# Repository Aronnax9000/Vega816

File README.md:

# Vega816 - Dual 65C816 Computer with Vector Pull rewrite

## Table of Contents

* [Functional Description](#functional-description)
* [CPU Buffer Board](#cpu-buffer-board)
* [DMA Control and Vector Pull Rewrite Shim](#dma-control-and-vector-pull-rewrite-shim)
    * [DMA Control Shim](#dma-control-shim)
    * [Vector Pull Rewrite Shim](#vector-pull-rewrite-shim)
    * [Offset of 7 triggers RESB interrupt handler for W65C816](#offset-of-7-triggers-resb-interrupt-handler-for-w65c816)
    * [Details of Vector Pull address rewriting](#details-of-vector-pull-address-rewriting)
    * [Effect of Vector Pull Rewrite in Emulation (65C02) Mode](#effect-of-vector-pull-rewrite-in-emulation-65c02-mode)
* [IRQ Dispatcher](#irq-dispatcher)
    * [IRQ Priority 7 to NMI Option](#irq-priority-7-to-nmi-option)
* [DMA Controller](#dma-controller)
    * [DMA Channels and Address Interleaving](#dma-channels-and-address-interleaving)
    * [How the DMA Controller routes requests](#how-the-dma-controller-routes-requests)
    * [DMA Request timing](#dma-request-timing)
* [Quad 64B I/O Bus](#quad-64b-i-o-bus)
* [Programmable Interrupt Controller (PIC)](#programmable-interrupt-controller-pic)
    * [2 Device PIC](#2-device-pic)
    * [Quad 2-Device PIC](#quad-2-device-pic)
* [16 MB Memory Decoder and Bus](#16-mb-memory-decoder-and-bus)
* [4 MB RAM + 32 K EEPROM Module](#4-mb-ram-32-k-eeprom-module)
* [Expansion Port to Single Device Ports](#expansion-port-to-single-device)
* [Single Device Port Breakouts](#single-device-port-breakouts)
* [Devices](#devices)
    * [W65C22 VIA Port](#w65c22-via-port)
    * [W65C51N ACIA (RS-232)](#w65c51n-acia-rs-232)
    * [8580/6581 SID](#8580-6581-sid)

* [VIA Port Devices](#via-port-devices)
    * [2x16 Character Display and front panel switches](#2x16-character-display-and-front-panel-switches)
    * [System Controller / SPI Controller](#system-controller-spi-controller)
    * [Ben Eater PS/2 Interface](#ben-eater-ps-2-interface)
    * [Commodore 64 CIA (VIA) #1](#commodore-64-cia-via-1)

## Functional Description

The Vega816 is a modular architecture for implementing symmetrical multiprocessing (SMP) with the Western Design Center W65C816 Microprocessor (aka 65816). The project takes as its starting point the 65816 breakout board designed by Adrien Kohlbecker, documented at [the project's GitHub page](https://github.com/adrienkohlbecker/BB816) as well as [Adrien's YouTube series](https://www.youtube.com/playlist?list=PLdGm_pyUmoII9D16mzw-XsJjHKi3f1kqT).

Support is provided for up to four bus mastering devices (four CPUs, or three CPUs and a video card) accessing up to four DMA channels, mapped into each CPU's address space.

## CPU Buffer Board

The CPU Buffer board provides two straight-wired connectors for the BB816 CPU breakout board, called "the CPU end", and buffers communications between the two of them and dual output connectors with the same pinout, called "the DMA end".

The extra straight wired connectors are included for ease of stacking the boards, both on the CPU end, and on the DMA end, in a multiplexed configuration, to implement shared memory multiprocessing. 

The circuit uses a 74AHCT245 octal bus transceiver for bi-directional communication for the 8 data lines, and seven 74HC541 octal buffers for the remaining signals provided by the BB816 CPU breakout board, including VPA and VDA. One of the buffers is allocated to CPU inputs (NMIB, IRQB, ABORTB, RDY_IN, etc), buffering signals from the DMA end. The remaining 74HC541s buffer lines from the CPU end onto the DMA end.

The bus transceiver and buffers' output enable lines are tied together and provided as an active low input called DMAB, so that a single signal suffices to turn communication on and off. A 1K pulldown resistor ensures that the board is active unless DMAB is raised high by external hardware.

## DMA Control and Vector Pull Rewrite Shim

If we assign each DMA channel its own address space, we can use address decoding in order to select which DMA channel is to be accessed by a particular CPU. In order to do that, we need to intercept the address lines from the CPU, pass decoding information to the DMA controller, and potentially rewrite the address being asserted by the CPU, before granting the CPU buffer access to the correct DMA channel.

The W65C816's VPB (Vector Pull) line also allows rewriting of the address asserted by the CPU when it is pulling an interrupt vector. It is convenient to provide hardware to intercept and rewrite the vector pull address as part of the same adapter.

Together, the DMA Control Shim and the Vector Pull Rewrite Shim provide facilities for DMA control and Vector Pull Rewrite to be performed by external hardware. 

### DMA Control Shim

The DMA Control shim provides movable jumpers for each of the bits A16-A23. Any of the bits may be selected as DMA_REQ. Once the jumper has been set to select one of those lines, it is connected as the DMA_REQ output, and disconnected from output to the DMA end, and is in fact pulled low on the DMA end (10K resistor), in order to map the request into a lower part of the DMA channel's address space.

The jumper offers the user a choice of granularity of DMA channel address mapping, in multiple of 2 increments from 64K (single bank, the minimum granularity) to 4M maximum. This allows for the address space to be contiguous across all DMA channels, depending on installed memory sizes. Ordinarily, this jumper should be set to the size of the maximum address space serviced by the hardware on either DMA channel, e.g. the total installed memory on that channel, or half the total memory across the two channels.

### Vector Pull Rewrite Shim

The Vector Pull Rewrite shim allows the IRQ Dispatcher to alter the fetch address of the processor when it is fetching an IRQ vector. A three bit number between 0-7 is added to the least significant bits (but one) of the fetch address, A1-A3, with carry into A4.

The VPB line is brought active low by the 65C816 during the fetch of any interrupt vector, not just IRQ. However, the standard IRQ vector's address has a unique bit pattern which makes it easy to autodetect, so that the shim will only request a vector pull offset when fetching the IRQ vector, and not for any other kind of interrupt.

When VPB is active (low) and A1-A3 are all high, indicating that an interrupt vector is being fetched by the processor, the shim requests a vector pull offset from the IRQ Dispatcher by asserting VP_REQ (positive logic). Pulldown resistors keep the offset equal to zero when Y0-Y2 are not connected (no IRQ Dispatcher) or in a high impedance state. 

A 74HC283 adder is used to add an offset to A1-A4 equal to the three bit number provided as input to the shim from the IRQ Dispatcher, on pins Y0-Y2. This has the effect of altering the fetch of the IRQ vector at $FFEE to a fetch of a vector at one of the following eight addresses: 
```
$00FFEE IRQ 0 
$00FFF0 IRQ 1 
$00FFF2 IRQ 2 
$00FFF4 IRQ 3 
$00FFF6 IRQ 4 
$00FFF8 IRQ 5 
$00FFFA IRQ 6 
$00FFFC RESET 
```
Y0-Y2 are pulled low by 10K resistors, for cases in which no Vector Pull controller is connected. Bypass jumpers are also provided for A1-A4, in case the 74HC283 adder and supporting logic are not installed.

The connector for the external Vector Pull Rewrite controller provides the E signal from the CPU, so that the Vector Pull Rewrite controller can know which scheme of vector pull (W65C02, W65C816) is being used.

#### Exposure of NMI and IRQ

The Vector Pull Rewrite shim exposes both IRQ and NMI to the IRQ Dispatcher. 

If the IRQ Dispatcher is not installed, a jumper on the Quad 64 IO Bus (IRQ Dispatch Bypass) should be installed to route IRQs to the common IRQ signal on the CPU via the CPU Buffer's DMA Channel connector.

When the IRQ Dispatcher is installed, the dispatcher takes responsibility for issuing IRQ to the CPU, via the Vector Pull Rewrite shim.

The exposure of NMI allows a device to raise an  IRQs at a selected IRQ priority level (say, IRQ 7) and instead trigger NMI, as the Commodore 64 RESTORE key did. The assertion of NMI is left under the control of the IRQ Dispatcher.

In scenarios where the IRQ Dispatcher is not installed, a jumper on the Quad 64B IO Bus (NMI Dispatch Bypass) can be used to direct IRQA7, IRQB7, both, or neither, to NMI.

#### Offset of 7 triggers RESB interrupt handler for W65C816

Note that, when the 65816 is running in native mode, if an IRQ priority of 7 (0x111) is asserted on Y0-Y2, the vector offset will result in the RESET vector being pulled. Since no actual hardware reset has occurred, if the reset handler relies on a hardware reset having taken place, unpredictable state may occur. It is generally advised to avoid the use of IRQ priority 7 when the CPU is in native mode. Alternatively, IRQ priority 7 may be rerouted to NMI, either through the IRQ Dispatcher, or a jumper on the Quad 64B IO Bus.

#### Details of Vector Pull address rewriting
The W65C816 datasheet gives this table of interrupt vectors which lie between $00FFE4 and $00FFFC
```
Address Function Last Octet (binary)
$00FFE4 COP      0x1110 0100
$00FFE6 BRK      0x1110 0110
$00FFE8 ABORT    0x1110 1000
$00FFEA NMI      0x1110 1010
$00FFEE IRQ      0x1110 1110
$00FFFC RESET    0x1111 1100
```
The datasheet also specifies that when the 65C816 is addressing an interrupt vector, it pulls its VPB line low. This is to allow the system to override the fetched interrupt vector with any other. 

VPB is pulled low for any interrupt vector fetch, not just IRQ, but the present design purposefully limits Vector Pull rewriting to only those cases when IRQ is the vector being fetched.

Note that the last nybble of each of the standard interrupt vectors is unique, which aids in designing a hook for any one of them (the same is true for 6502 Emulation mode, see below). A test of these four bits suffices to uniquely identify the vector being pulled. In particular, both bytes of the two-byte IRQ vector ($FFEE and $FFEF) are the only two bytes in this table with $E or $F (0x1110, 0x1111) as the last nybble of address, i.e., A1-A3 high.

Note also the gap of 12 bytes between the IRQ vector and the RESET vector. Since each vector occupies two bytes, this gap provides sufficient space to specify six (6) additional vectors. 

```
$00FFE4 COP	
$00FFE6 BRK
$00FFE8 ABORT 
$00FFEA NMI 
$00FFEE IRQ 0 
$00FFF0 IRQ 1 
$00FFF2 IRQ 2 
$00FFF4 IRQ 3 
$00FFF6 IRQ 4 
$00FFF8 IRQ 5 
$00FFFA IRQ 6 
$00FFFC RESET 
```
If an offset 0-6 is added to A1-A3, (leaving A0 as found), then the vector fetched will be as shown above, going forward from IRQ0.

#### Effect of Vector Pull Rewrite in Emulation (65C02) Mode
The 6502's IRQ vector, like its 65816 counterpart, has 0x111x in the last nybble, so it is detected by the Vector Pull Rewrite Shim. 
```
$FFFA NMI
$FFFC RESB
$FFFE BRK/IRQ 
```
Unlike the 65816's IRQ vector, the 6502 IRQ vector occurs at the very top of its page, so additions of 1-7 to the bits may force A4 to overflow to 0 (no carry). In particular, $FFFE + $02 = $FFE0, etc. This means the augmented
IRQ vector map for the 6502 looks like this:

```
$FFE0 BRK/IRQ 1
$FFE2 BRK/IRQ 2
$FFE4 BRK/IRQ 3
$FFE6 BRK/IRQ 4
$FFE8 BRK/IRQ 5
$FFEA BRK/IRQ 6
$FFEC BRK/IRQ 7
...
$FFFA NMI
$FFFC RESB
$FFFE BRK/IRQ 0
```
## IRQ Dispatcher

Devices mapped within the physical address space of either DMA channel may raise interrupt requests against either CPU. For each CPU, an 8-to-3 priority encoders is used to prioritize eight different levels of IRQ, from 0-7, with lower values meaning higher priority.

The priority is encoded as a three bit offset and offered to the Vector Pull Rewrite shim, on pins Y0-Y2, where it is used to offset the fetch addresses of the CPU's next two-byte IRQ vector pull. 

IRQs received from DMA channel 0 and intended for CPU A or CPU B will be routed to those CPUs. 

For IRQs received from DMA channel 1, the situation is reversed: IRQs which DMA channel 1 intended for CPU A will be routed to CPU B, and vice versa. This crossover in routing means that the CPU target values in the system's PIC controllers always refer to the same physical CPU. I.e., CPU A is always target 0, and CPU B is always target 1, no matter on which DMA channel a PIC is installed. The crossover is reflected in the connector placement on the IRQ Dispatcher: no crossover cable is needed.

### IRQ Priority 7 to NMI Option

The combined IRQ signals are diode-NANDed together to drive IRQ on the CPU through the Vector Pull Rewrite shim. IRQ priorities 0-6 are NANDed together first, with priority 7 NANDed to the result unless jumper IRQA7 or IRQB7 are set to direct priority 7 to NMI to CPU A or CPU B.

Rerouting IRQ Priority 7 to NMI is offered elsewhere in the design, as a jumper on the Quad 64B IO Bus, for cases where no IRQ Dispatcher and/or Vector Pull Rewrite shim is installed. See the documentation on the Quad 64B IO Bus.

## DMA Controller

The DMA Controller is intended to control the multiplexing of one or two CPUs (called CPU A and CPU B) onto one or two communication channels (called DMA 0 and DMA 1). The two channels are cross-mapped in address space from the point of view of opposite processors, depending on a selected granularity. For example, if 64 KB (single bank) granularity is selected, when CPU A requests Bank 0, the DMA controller will connect it to DMA channel 0, whereas if CPU A requests Bank 1, the controller will connect it to DMA channel 1. The situation is reversed for CPU B. The controller will direct its requests for Bank 0 to DMA channel 1, and requests for Bank 1 to DMA channel 0.

This permits each CPU to have its Bank 0 lie within the address space of a separate physical DMA channel, so that accesses by each CPU to its own Bank 0 will not normally interfere with the opposite CPU's requests for its own Bank 0.

The effect for higher memory is that each CPU's odd numbered banks are the other CPU's even numbered banks, interleaved to the top of physical memory.

The granularity of the interleaving is specified by a jumper on the DMA Controller Shim, and provided to the DMA controller as the signal DMA_REQ. Additionally, the following CPU signals are utilized in implementing DMA:
```
RDY_IN
ABORTB
VA
```
Since the DMA controller will dispatch requests from up to two CPUs, CPU A and CPU B, the signals are distinguished within the controller with these designations:

Inputs
```
DMA_REQB_A DMA_REQB_A
RDY_IN_A  RDY_IN_B
ABORTB_A  ABORTB_B
VA_A      VA_B
```
Since the DMA channels are cross-mapped in address range between the two CPUs, so that each CPU's DMA 0 corresponds to the lower part of its address space with respect to DMA 1, the outputs are:
```
DMA_0_A  = DMA_1_B
DMA_1_A  = DMA_0_B
```
This cross mapping, which takes place in the connector wiring of the DMA Controller board, means that two identically configured units may be connected as CPU A or CPU B, provided that their DMA buffer modules are connected with the sense of DMA 0 and DMA 1 reversed.

The "home" channel for a CPU is the DMA channel containing that CPU's Bank Zero.

Here are the possible scenarios for DMA arbitration:

1. Both CPUs are asserting valid address, each against their own home DMA channels. CPU A is using DMA 0, and CPU B is using DMA 1.
2. Both CPUs are asserting valid address, against the opposite CPU's home DMA channel. CPU A is asserting against DMA 1, and CPU B is asserting against DMA 0.
3. Both CPUs are asserting valid address against the same DMA channel. CPU A is asserting against DMA 0, and so is CPU B.
4. Both CPUs are asserting valid address against the same DMA channel. CPU A is asserting against DMA 1, and so is CPU B.

The DMA controller monitors the VA (Valid Address) from one or two CPUs, as well as an additional input, DMA_REQB. If one CPU asserts DMA_REQB, the controller checks the VA line from the opposite CPU. If it is not active, the controller asserts DMA

### DMA Channels and Address Interleaving

When no request granularity is set for a CPU on the DMA Control Shim, all DMA requests take place against DMA 0.

If only the primary granularity is set, DMA requests will take place against DMA 0 and DMA 2.
If only the secondary granularity is set, DMA requests will take place against DMA 0 and DMA 1.

If both granularities are set, DMA requests will take place against DMA 0-3. The maximum granularity for four channel DMA is 4 MB, with primary set at 8 MB and secondary set at 4MB. (0x1100 0000). In that case,

```
Requests for the range 
(0x00?? ????) go to DMA channel 0
(0x01?? ????) go to DMA channel 1
(0x10?? ????) go to DMA channel 2
(0x11?? ????) go to DMA channel 3
```

The DMA controller maps requests so that each CPU sees a different DMA channel as its channel 0, with subsequent channels in order. The next CPU's channel 0 is the present CPU's channel 1, and channel 0 for the next CPU after that is channel 2. The order wraps to form a closed ring.

```
           Requested           Physical
CPU   A    B      C      D
      0    1      2      3      DMA 0
      1    2      3      0      DMA 1
      2    3      0      1      DMA 2
      3    0      1      2      DMA 3
```

From the chart it can be seen that the channel that CPU A sees as DMA 0 is seen by CPU B as DMA channel 3, etc.

DMA request granularity may or may not match the largest installed address size.

Since the address bits used to select the DMA channels are suppressed in the address presented to the destination channel, if a CPU's request granularity is set to a smaller value than the installed memory size on any given DMA channel, then a range of that memory will not be accessible to that CPU.

CPU A has primary DMA on 1M, and secondary DMA set to 512K. 
CPU A issues requests against Banks 0 to 7.

What DMA channels are addressed?

```
0x000 Bank 0x000 0 on DMA 0
0x001 Bank 0x000 0 on DMA 1
0x010 Bank 0x000 0 on DMA 2
0x011 Bank 0x000 0 on DMA 3
0x100 Bank 0x100 4 on DMA 0
0x101 Bank 0x100 4 on DMA 1
0x110 Bank 0x100 4 on DMA 2
0x111 Bank 0x100 4 on DMA 3
```

### How the DMA Controller routes requests

Each request enters the DMA controller as a two bit code, representing the two address lines selected by jumper settings on the DMA Control Shim. These two bits are augmented with a third bit, a CPU Priority bit supplied for that CPU. The CPU Priority bit is active low, and pulled high. 

The three bit request is decoded into a one in eight choice, each representing a request for one of four DMA channels, with and without priority. The eight decoded request lines are then routed, together with the decoded request lines from the other CPUs, into priority encoders, one for each of the four DMA channels. The eight request lines entering each DMA channel's priority encoder are wired so that the four priority requests occur with highest priority, followed by the four no-priority request lines. Among the two sets of priority requests, Each DMA channel gives greatest priority to a particular CPU, followed by the others in ring order.

```
DMA Channel   Order
     0        ADCB                  
     1        BADC            
     2        CBAD
     3        DCBA            
```

When more than one CPU requests the same DMA channel, the losing CPU(s) must be informed, since they will not have access to the DMA channel for the duration of the current clock cycle. 

The W65C816 provides two mechanisms for this, the READY signal, and the ABORTB interrupt signal. The READY signal pauses the processor, if pulled low. Releasing the low condition, allowing READY to return high, will cause the CPU to resume processing on the rising edge of the next clock cycle.

Adrien Kohlbecker's BB816 CPU breakout provides the input to the READY signal as RDY_IN. This signal is that which is used by the DMA Controller to pause the CPU.

If the losing CPU is losing access to its Bank Zero channel (due to the winning CPU having priority bit active), the losing CPU is paused, by pulling RDY_IN low. 

Any other losing CPU is informed by pulling the losing CPU's ABORTB low, triggering the losing CPU's ABORT Interrupt handler. In most cases, the handler will simply return control to the interrupted process so that another attempt at access to the DMA channel can be made on the next clock cycle.

### DMA Request timing

CPU to DMA routing must be complete, with time to spare for the devices on the DMA channel to decode incoming address, before the routing is latched in on the falling edge of the clock. Now latched, the CPU to DMA channel routing persists through the remainder of the clock cycle, until unlatched at the rising edge of the clock at the beginning of the next cycle, so that arbitration may begin again.

## Quad 64B I/O Bus
The I/O bus board decodes a selected page (256 bytes) of address space for device I/O, together with a corresponding range in the the page immediately above it, for use by I/O devices.
3
Jumpers set the base I/O address space on any even-numbered page boundary in Bank Zero. The page of address space immediately above the base I/O page is reserved for configuring the programmable interrupt controller (PIC). For example, if the bus is set so that its base address is $0200, then page $0300 is reserved for use by the PIC.

The odd numbered page immediately above the base page is used by the programmable interrupt controller to store IRQ priority and CPU target information for use in forwarding interrupt requests issued by devices under PIC control.

In order to avoid the default page zero and stack areas at $0000 and $01000, it is advisable to avoid setting the I/O base address to page $00, leaving 63 possible pages between $0200-$7E00.

Four I/O expansion ports are provided, each spanning 64 bytes of the assigned I/O page. Each port is provided with a one-in-four chip select signal based on further decoding of the address, into 16 byte ranges areas. 
Standard connections are provided for adding a CS Decode module which can perform finer and/or coarser grained address decoding into 64, 32, and 8 byte I/O address ranges.

The 16 byte range chip select signals are raised high for both the I/O page within that 16 byte range, as well as for that range in the page immediately above it. E.g., if a device is mapped to $0210-$021F, then the chip select for that device is also active for the range $0310-$031F. This allows access to latches used to store programmable interrupt configuration, and potentially other metadata used in controlling the device.

The 16 IRQ output lines from each expansion port (8 priorities destined for one of up to two CPUs) are multiplexed via diode logic for dispatch by the IRQ Dispatch board.

## Programmable Interrupt Controller (PIC)

### 2 Device PIC
The programmable interrupt controller accepts active low IRQ inputs from up to two sources. For each source, the PIC generates an interrupt signal at one of eight pre-selectable priorities (0-7), and directs the interrupt to a preselected one of two target CPUs. The PIC uses diode logic so that interrupts generated by multiple PICs may be placed on the same IRQ bus. 

The IRQ bus terminates at the IRQ Dispatcher, where 10K pull-up resistors ensure that lines on the IRQ bus are held high, unless pulled low by an interrupt signal originating at a PIC.

### Quad 2-Device PIC
A 64-byte expansion slot may include a programmable interrupt controller. The PIC subdivides the 64 byte address range into eight 8-byte device I/O spaces, two for each of the 16-byte address ranges decoded by the expansion bus controller and supplied to the PIC as chip select lines. 

Both IRQ priority (0-7) and CPU destination (CPU A or CPU B) can be programmed for each of up to eight devices, by writing to latches which shadow the device I/O space in the next higher page of address space. Four octal latches, at address offsets +$100, +$104, +$108 and +$10C offsets from the corresponding 16 byte I/O address ranges are provided. Each octal latch stores programmable interrupt information for up to two 8 byte devices: the low nybble for an eight byte device at offset +$00 from the base I/O address, and the high nybble for an eight byte device at offset $08 from the base I/O address. The low bit of the nybble determines the target CPU. The high three bits specify the priority from 0-7.

## 16 MB Memory Decoder and Bus

## 4 MB RAM + 32 K EEPROM Module

## Expansion Port to Single Device

The 64-byte expansion slots provided by the Expansion Bus may be broken out into individual device I/O ports spanning 64, 32, 16, or 8 bytes of address space. The four 16-byte chip select lines are further decoded by the programmable interrupt controller down to two 8-byte chip select lines per 16 byte range.

These sample breakouts show a complete breakout of one port into 1x64, 2x32, 4x16 and 8x8 byte device ports. Also shown is a reduction of this most general breakout into a sample breakout capable of supporting 3 VIAs and 2 ACIAs.

## Single Device Port Breakouts
A single 64, 32, or 16 byte device port may be further adapted to serve multiple devices of smaller address range. This approach introduces an extra address decoding delay compared with the above approach of adapting expansion bus directly.

## Devices

### W65C22 VIA Port

This device presents the 20 outward facing lines of a VIA port, plus power and ground.

### W65C51N ACIA (RS-232)

This device supplies an RS-232 serial port.

## VIA Port Devices

### 2x16 Character Display and front panel switches

### System Controller / SPI Controller

The System Controller / SPI Controller is a VIA port device providing software control over system hardware.

Port A controls clock speed, CPU B RDY_IN and DMA priority control, and EEPROM banking on each of the DMA channels.

On system reset:

* CPU B is paused
* both CPUs are set to slow clock
* CPU B DMA Priority is turned off. CPU B will not be able to unilaterally deassert RDY_IN on CPU A for DMA operations.
* EEPROM on DMA 0 is set to read, with writes to the ROM area taking place against underlying RAM.
* EEPROM on DMA 1 is set to read, with writes to the ROM area taking place against underlying RAM.

A typical startup sequence would consist of these steps:

* CPU A copies EEPROM on DMA 0 to underlying RAM.
* CPU A copies EEPROM on DMA 1 to underlying RAM, or otherwise populates RAM underlying the DMA 1 ROM area.
* CPU A banks out EEPROMs for both read and write
* CPU A sets high clock speed for CPU A and CPU B
* If desired, CPU B is given DMA priority (e. g. for video processing).
* CPU A asserts RDY_IN on CPU B, permitting CPU B to start processing with CPU B's RESET vector.

Port B provides SPI communication, with SCK, MISO, MOSI lines, and three chip select lines, which in turn drive a 74AHC138 3-to-8 controller to select one of eight external SPI devices. PB6 and PB7 are reserved for pulse generation and pulse counting purposes (see W65C22 datasheet).

### Ben Eater PS/2 Interface

### Commodore 64 CIA (VIA) #1

### 8580/6581 SID

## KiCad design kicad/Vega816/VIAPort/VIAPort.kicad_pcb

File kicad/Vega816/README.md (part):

# Vega816 - DMA Arbitration and VPB Rewrite for BB816 Breakout

The Vega816 is a SMP (Symmetrical Multiprocessing) architecture for Adrien Kohlbecker's 65816
Breakout Board, part of Adrien's astonishingly meticulous BB816 project. 
Hereinafter, unless otherwise specified, "CPU" refers to the W65C816S as wrapped 
in Adrien's W65C816 Breakout Board, or other device (e.g. GPU) made to expose relevant features of
the same interface. The current schematics reference BB816 Breakout Board Revision A.27.

The Vega816 allows up to four CPUs or other bus mastering devices shared access 
to up to four DMA channels, designated DMA0 to DMA3. Each DMA channel provides a
full 16 MB of address space. To ensure that each CPU has its own independent Bank Zero
at startup, each CPU has an independent physical DMA channel as its own "home" DMA0,
with the remaining channels numbered in circular fashion. 

As an independent feature, Vector Pull Rewrite is implemented, providing up to 8 separate
possible IRQ vectors, IRQB0-IRQB7. When an IRQ is asserted on one of the eight provided IRQ inputs,
a priority encoder calculates a three bit offset, and adds double this number to the address
being fetched by the CPU when an IRQ Vector Pull is detected (vectors occupy two bytes, accounting
for the doubled offset used to fetch both bytes). 

The Vector Pull Rewrite Feature works in either Emulation or Native mode.

## Implementation Details

Each CPU is mounted in a "CPU Shim", with identical input and output connectors each wired to 
the BB816 Breakout Board standard. The CPU Shim provides hardware hooks for connecting a DMA Controller,
and eight separate IRQ inputs used by the IRQ Priority Vector Pull Rewrite feature, which is 
also provided by the CPU Shim. 

Both the DMA Control section and the Vector Pull Rewrite section
may alter input and output between the CPU and the bus. For example, since the DMA process 
may result in a change to A23-A22, the BANK0B line is recalculated, so that the value on the bus
reflects whether Bank Zero is being requested on the destination DMA channel.

The CPU Shim is mounted on the CPU Buffer Board, which buffers access between the CPU and one out of 
up to four physical DMA channels. Each DMA channel on the buffer board replicates the full 
BB816 Breakout Board interface. Any hardware built to accept a BB816 Breakout Board 
as its CPU can be attached to a DMA channel without modification. 

The CPU Buffer takes a 1-of-4 input which switches on one of the four physical DMA channel
buffers. 

When not enabled, each DMA channel is in a high impedance state. This allows the buffer 
boards to be "stacked": DMA channels from separate boards may be physically connected 
together so that multiple CPUs share multiple DMA channels. If very long/tall pin headers
are installed, the boards may be physically stacked one atop another. 

When DMA requests are not enabled for a particular CPU, it will always request DMA0. 
When DMA requests are enabled for a particular CPU, the lines A23 and A22 are
decoded as the requested DMA channel and passed to the DMA Controller, along with a priority bit
setting.  

A four channel DMA Controller accepts requests from up to four CPUs, and uses priority decoding
logic to assign CPUs to DMA channels on each clock cycle. A CPU which does not
"win" access to its requested DMA channel is "paused" for one cycle. A pulse is
applied to that CPU's READY_IN, causing it to pause until the falling edge of the next
clock cycle.

Under ordinary circumstances, a CPU always wins priority access to the DMA 
channel that it has designated DMA0. If another CPU (GPU) needs access to
another CPU's DMA0, it will be paused, unless it also has asserted a "Priority Bit"
to the DMA Controller. In that case, the CPU whose home DMA0 channel has been
requested by the visiting CPU will be paused, instead, and the visiting
CPU will be granted access. This feature supports real time applications 
such as VIC-II and World's Worst Video Card style DMA.

Each CPU is mounted on a CPU Shim, consisting of a DMA Shim and Vector Pull Rewrite Shim.

The DMA Control Shim monitors CPU address lines and, when the CPU is in Native mode,
issues DMA requests to the DMA Controller. The DMA Controller performs bus arbitration among
the installed CPUs. If a CPU wins access to a DMA channel for a given clock cycle,
its DMA Control Shim receives the go-ahead from the DMA Controller, and switches on the
correct channel on the CPU's CPU Buffer. Otherwise, the DMA Control Shim pauses its
CPU, by asserting RDY_IN low.

The Vector Pull Rewrite Shim allows eight levels of IRQ priority from 0-7. Priority 7 may be 
rerouted to perform NMI instead. When one of the IRQ inputs not designated for NMI
is pulled low, the VPB Rewrite Shim pulls IRQ low on the CPU, and
monitors VPB and A0-A8 to detect when the interrupt vector is pulled by the CPU in response.
The VPB Rewrite Shim then modifies the fetched vector's address by adding an even number
offset between 0 and 14 to the vector fetch address. The number is calculated as twice the
highest IRQ Priority of the current asserted IRQs.
    
## Functional Description

The Vega816 is a modular architecture for implementing symmetrical multiprocessing (SMP) with the Western Design Center W65C816 Microprocessor (aka 65816). The project takes as its starting point the 65816 breakout board designed by Adrien Kohlbecker, documented at [the project's GitHub page](https://github.com/adrienkohlbecker/BB816) as well as [Adrien's YouTube series](https://www.youtube.com/playlist?list=PLdGm_pyUmoII9D16mzw-XsJjHKi3f1kqT).

Support is provided for up to four bus mastering devices (four CPUs, or three CPUs and a video card) accessing up to four DMA channels. Each DMA channel has full 24 bit addressing and therefore 16 MB of address space.

Through the use of software programmable banking registers, all four CPUs share access to all four 16 MB DMA channels, for a total of 64 MB of shared memory.

The architecture can be extended in a star pattern to form massively parallel networks, by connecting one DMA channel from one node as an input CPU channel on a higher-order node in the hierarchy.

The DMA Control shim provides movable jumpers for each of the bits A16-A23. Any of the bits may be selected as DMA_REQ. Once the jumper has been set to select one of those lines, it is connected as the DMA_REQ output, and disconnected from output to the DMA end, and is in fact pulled low on the DMA end (10K resistor), in order to map the request into a lower part of the DMA channel's address space.

The jumper offers the user a choice of granularity of DMA channel address mapping, in multiple of 2 increments from 64K (single bank, the minimum granularity) to 4M maximum. This allows for the address space to be contiguous across all DMA channels, depending on installed memory sizes. Ordinarily, this jumper should be set to the size of the maximum address space serviced by the hardware on either DMA channel, e.g. the total installed memory on that channel, or half the total memory across the two channels.

# Vector Pull Rewrite 

The Vector Pull Rewrite feature allows the IRQ Dispatcher to alter the fetch address of the processor when it is fetching an IRQ vector. A three bit number between 0-7 is added to the least significant bits (but one) of the fetch address, A1-A3, with carry into A4.

The VPB line is brought active low by the 65C816 during the fetch of any interrupt vector, not just IRQ. However, the standard IRQ vector's address has a unique bit pattern which makes it easy to autodetect, so that the shim will only request a vector pull offset when fetching the IRQ vector, and not for any other kind of interrupt.

When VPB is active (low) and A1-A3 are all high, indicating that an interrupt vector is being fetched by the processor, the shim requests a vector pull offset from the IRQ Dispatcher by asserting VP_REQ (positive logic). Pulldown resistors keep the offset equal to zero when Y0-Y2 are not connected (no IRQ Dispatcher) or in a high impedance state. 

A 74HC283 adder is used to add an offset to A1-A4 equal to the three bit number provided as input to the shim from the IRQ Dispatcher, on pins Y0-Y2. This has the effect of altering the fetch of the IRQ vector at $FFEE to a fetch of a vector at one of the following eight addresses: 
```
$00FFEE IRQ 0 
$00FFF0 IRQ 1 
$00FFF2 IRQ 2 
$00FFF4 IRQ 3 
$00FFF6 IRQ 4 
$00FFF8 IRQ 5 
$00FFFA IRQ 6 
$00FFFC RESET 
```
Y0-Y2 are pulled low by 10K resistors, for cases in which no Vector Pull controller is connected. Bypass jumpers are also provided for A1-A4, in case the 74HC283 adder and supporting logic are not installed.

The connector for the external Vector Pull Rewrite controller provides the E signal from the CPU, so that the Vector Pull Rewrite controller can know which scheme of vector pull (W65C02, W65C816) is being used.

#### Exposure of NMI and IRQ

The Vector Pull Rewrite shim exposes both IRQ and NMI to the IRQ Dispatcher. 

If the IRQ Dispatcher is not installed, a jumper on the Quad 64 IO Bus (IRQ Dispatch Bypass) should be installed to route IRQs to the common IRQ signal on the CPU via the CPU Buffer's DMA Channel connector.

When the IRQ Dispatcher is installed, the dispatcher takes responsibility for issuing IRQ to the CPU, via the Vector Pull Rewrite shim.

The exposure of NMI allows a device to raise an  IRQs at a selected IRQ priority level (say, IRQ 7) and instead trigger NMI, as the Commodore 64 RESTORE key did. The assertion of NMI is left under the control of the IRQ Dispatcher.

In scenarios where the IRQ Dispatcher is not installed, a jumper on the Quad 64B IO Bus (NMI Dispatch Bypass) can be used to direct IRQA7, IRQB7, both, or neither, to NMI.

#### Offset of 7 triggers RESB interrupt handler for W65C816

Note that, when the 65816 is running in native mode, if an IRQ priority of 7 (0x111) is asserted on Y0-Y2, the vector offset will result in the RESET vector being pulled. Since no actual hardware reset has occurred, if the reset handler relies on a hardware reset having taken place, unpredictable state may occur. It is generally advised to avoid the use of IRQ priority 7 when the CPU is in native mode. Alternatively, IRQ priority 7 may be rerouted to NMI, either through the IRQ Dispatcher, or a jumper on the Quad 64B IO Bus.

#### Details of Vector Pull address rewriting
The W65C816 datasheet gives this table of interrupt vectors which lie between $00FFE4 and $00FFFC
```
Address Function Last Octet (binary)
$00FFE4 COP      0x1110 0100
$00FFE6 BRK      0x1110 0110
$00FFE8 ABORT    0x1110 1000
$00FFEA NMI      0x1110 1010
$00FFEE IRQ      0x1110 1110
$00FFFC RESET    0x1111 1100
```
The datasheet also specifies that when the 65C816 is addressing an interrupt vector, it pulls its VPB line low. This is to allow the system to override the fetched interrupt vector with any other. 

VPB is pulled low for any interrupt vector fetch, not just IRQ, but the present design purposefully limits Vector Pull rewriting to only those cases when IRQ is the vector being fetched.

Note that the last nybble of each of the standard interrupt vectors is unique, which aids in designing a hook for any one of them (the same is true for 6502 Emulation mode, see below). A test of these four bits suffices to uniquely identify the vector being pulled. In particular, both bytes of the two-byte IRQ vector ($FFEE and $FFEF) are the only two bytes in this table with $E or $F (0x1110, 0x1111) as the last nybble of address, i.e., A1-A3 high.

Note also the gap of 12 bytes between the IRQ vector and the RESET vector. Since each vector occupies two bytes, this gap provides sufficient space to specify six (6) additional vectors. 

```
$00FFE4 COP	
$00FFE6 BRK
$00FFE8 ABORT 
$00FFEA NMI 
$00FFEE IRQ 0 
$00FFF0 IRQ 1 
$00FFF2 IRQ 2 
$00FFF4 IRQ 3 
$00FFF6 IRQ 4 
$00FFF8 IRQ 5 
$00FFFA IRQ 6 
$00FFFC RESET 
```
If an offset 0-6 is added to A1-A3, (leaving A0 as found), then the vector fetched will be as shown above, going forward from IRQ0.

#### Effect of Vector Pull Rewrite in Emulation (65C02) Mode
The 6502's IRQ vector, like its 65816 counterpart, has 0x111x in the last nybble, so it is detected by the Vector Pull Rewrite Shim. 
```
$FFFA NMI
$FFFC RESB
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
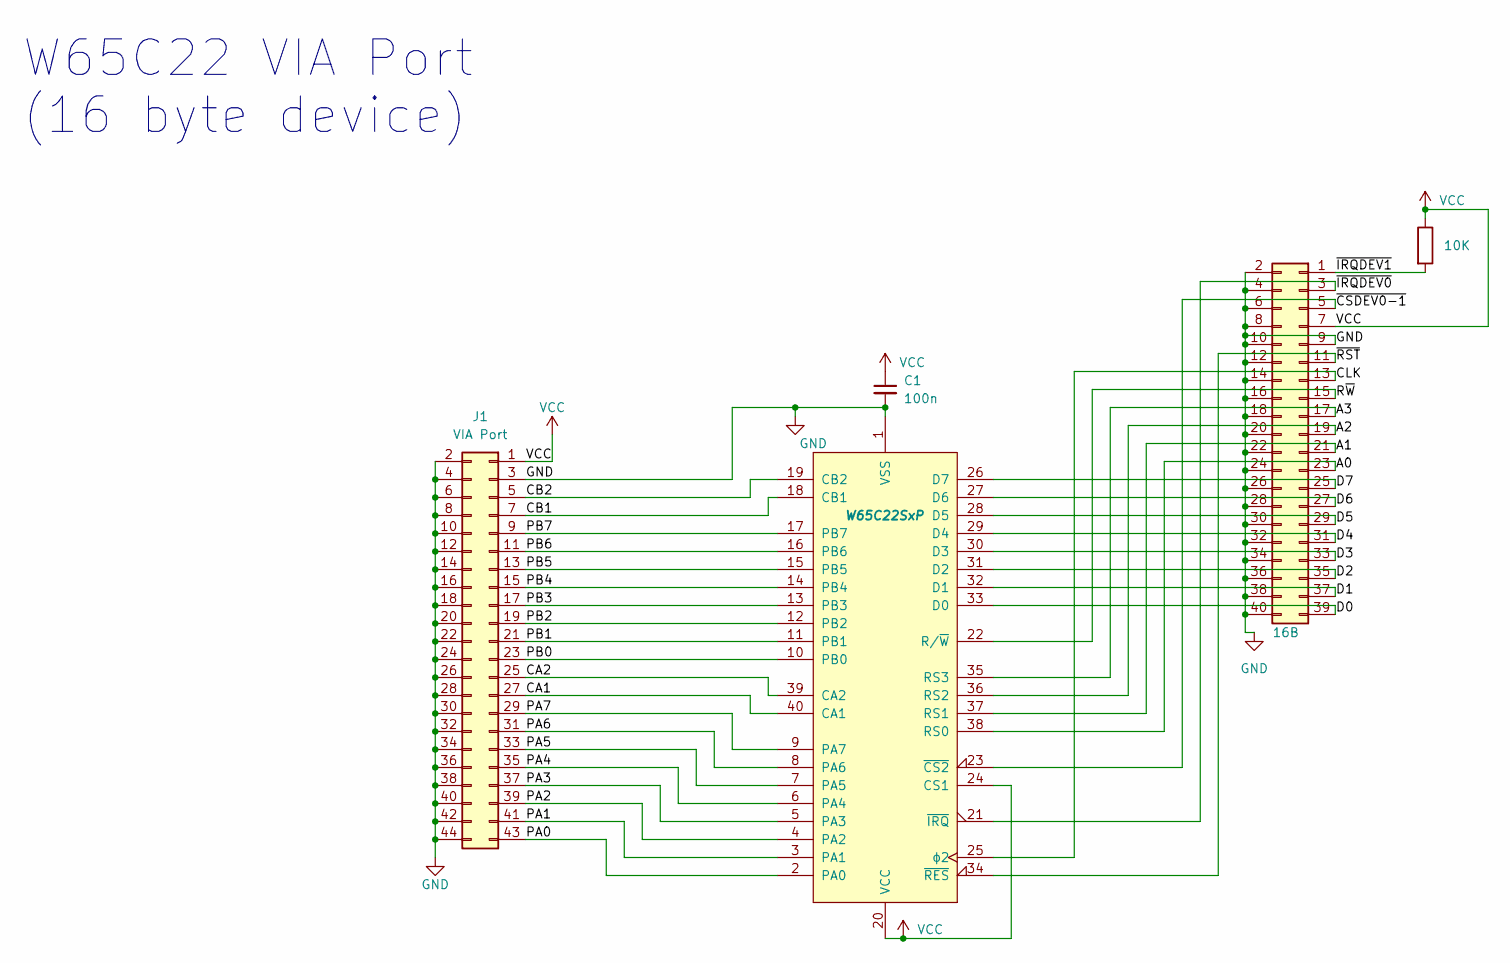
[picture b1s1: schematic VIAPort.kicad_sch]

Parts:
C1: 100n; C_Disc_D3.4mm_W2.1mm_P2.50mm
J1: VIA Port; PinSocket_2x21_P2.54mm_Vertical
J2: 16B; PinSocket_2x20_P2.54mm_Vertical
R1: 10K; R_Axial_DIN0207_L6.3mm_D2.5mm_P7.62mm_Horizontal
U1: W65C22SxP; DIP-40_W15.24mm_Socket

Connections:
/A0: J2.23, U1.38 (RS0)
/A1: J2.21, U1.37 (RS1)
/A2: J2.19, U1.36 (RS2)
/A3: J2.17, U1.35 (RS3)
/CA1: J1.27, U1.40 (CA1)
/CA2: J1.25, U1.39 (CA2)
/CB1: J1.7, U1.18 (CB1)
/CB2: J1.5, U1.19 (CB2)
/CLK: J2.13, U1.25 (ϕ2)
/D0: J2.39, U1.33 (D0)
/D1: J2.37, U1.32 (D1)
/D2: J2.35, U1.31 (D2)
/D3: J2.33, U1.30 (D3)
/D4: J2.31, U1.29 (D4)
/D5: J2.29, U1.28 (D5)
/D6: J2.27, U1.27 (D6)
/D7: J2.25, U1.26 (D7)
/PA0: J1.43, U1.2 (PA0)
/PA1: J1.41, U1.3 (PA1)
/PA2: J1.39, U1.4 (PA2)
/PA3: J1.37, U1.5 (PA3)
/PA4: J1.35, U1.6 (PA4)
/PA5: J1.33, U1.7 (PA5)
/PA6: J1.31, U1.8 (PA6)
/PA7: J1.29, U1.9 (PA7)
/PB0: J1.23, U1.10 (PB0)
/PB1: J1.21, U1.11 (PB1)
/PB2: J1.19, U1.12 (PB2)
/PB3: J1.17, U1.13 (PB3)
/PB4: J1.15, U1.14 (PB4)
/PB5: J1.13, U1.15 (PB5)
/PB6: J1.11, U1.16 (PB6)
/PB7: J1.9, U1.17 (PB7)
/R~W: J2.15, U1.22 (R/~W)
/~CSDEV0-1: J2.5, U1.23 (~CS2)
/~IRQDEV0: J2.3, U1.21 (~IRQ)
/~IRQDEV1: J2.1, R1.2
/~RST: J2.11, U1.34 (~RES)
GND: C1.2, J1.2, J1.3, J1.4, J1.6, J1.8, J1.10, J1.12, J1.14, J1.16, J1.18, J1.20, J1.22, J1.24, J1.26, J1.28, J1.30, J1.32, J1.34, J1.36, J1.38, J1.40, J1.42, J1.44, J2.2, J2.4, J2.6, J2.8, J2.9, J2.10, J2.12, J2.14, J2.16, J2.18, J2.20, J2.22, J2.24, J2.26, J2.28, J2.30, J2.32, J2.34, J2.36, J2.38, J2.40, U1.1 (VSS)
VCC: C1.1, J1.1, J2.7, R1.1, U1.20 (VCC), U1.24 (CS1)

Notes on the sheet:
W65C22 VIA Port (16 byte device)

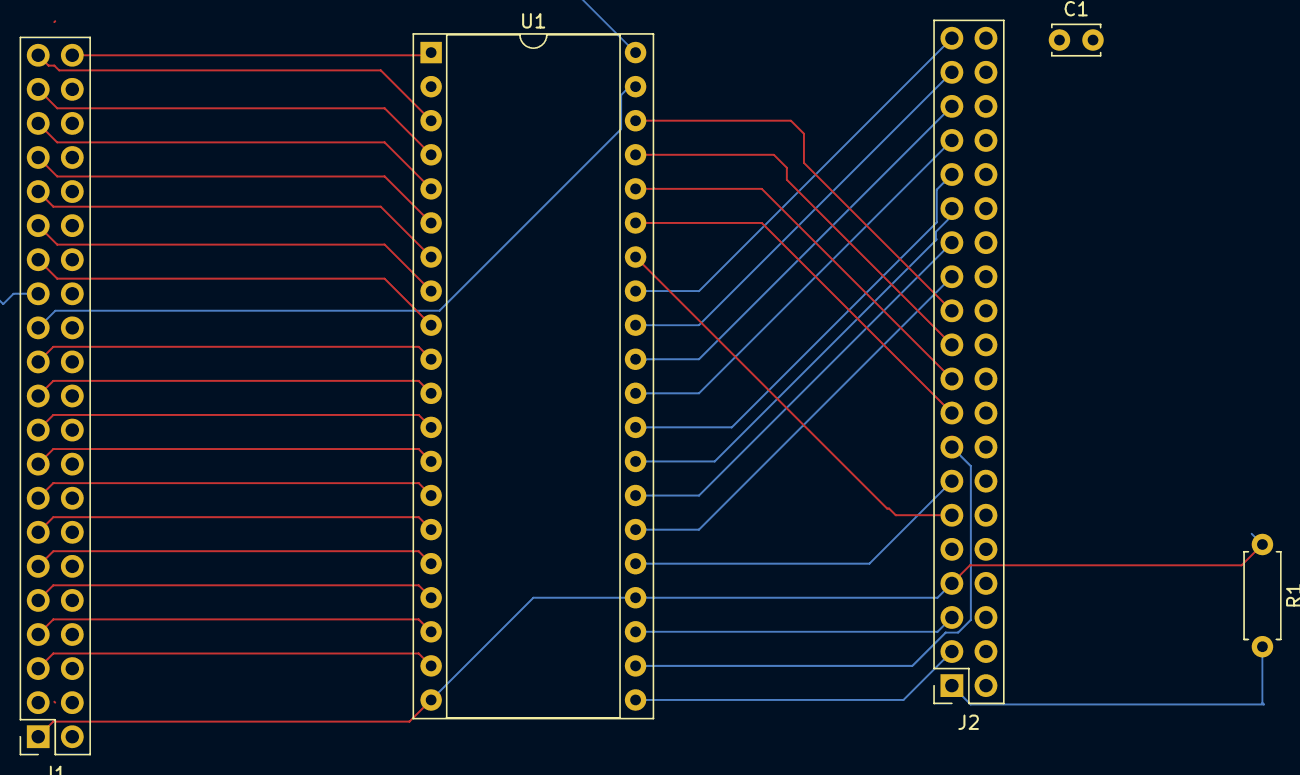
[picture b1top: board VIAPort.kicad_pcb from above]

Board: 4 copper layers, 5 parts (0 on the bottom side), 39 nets.

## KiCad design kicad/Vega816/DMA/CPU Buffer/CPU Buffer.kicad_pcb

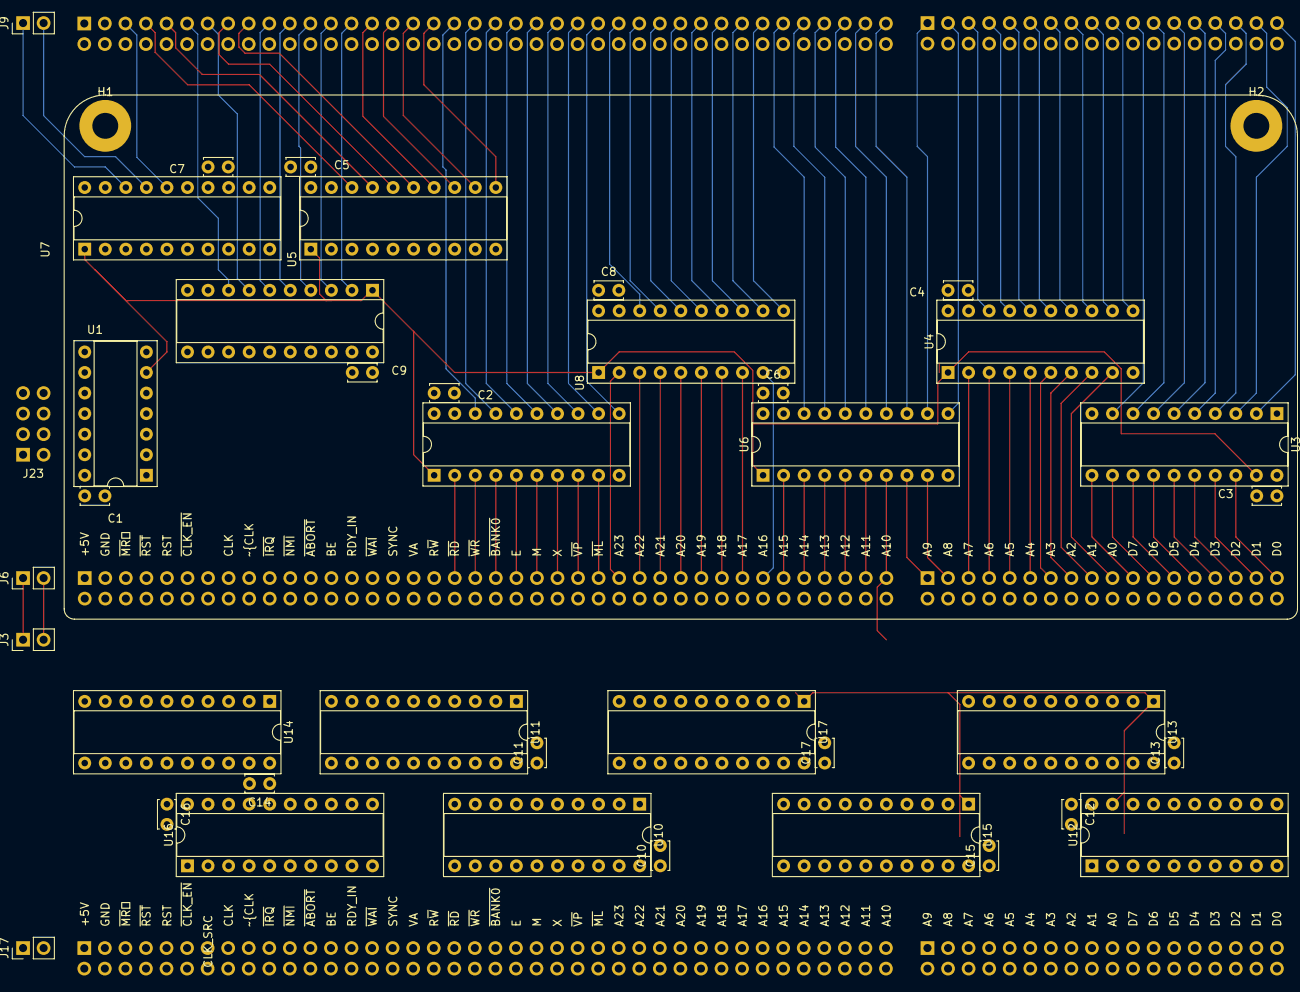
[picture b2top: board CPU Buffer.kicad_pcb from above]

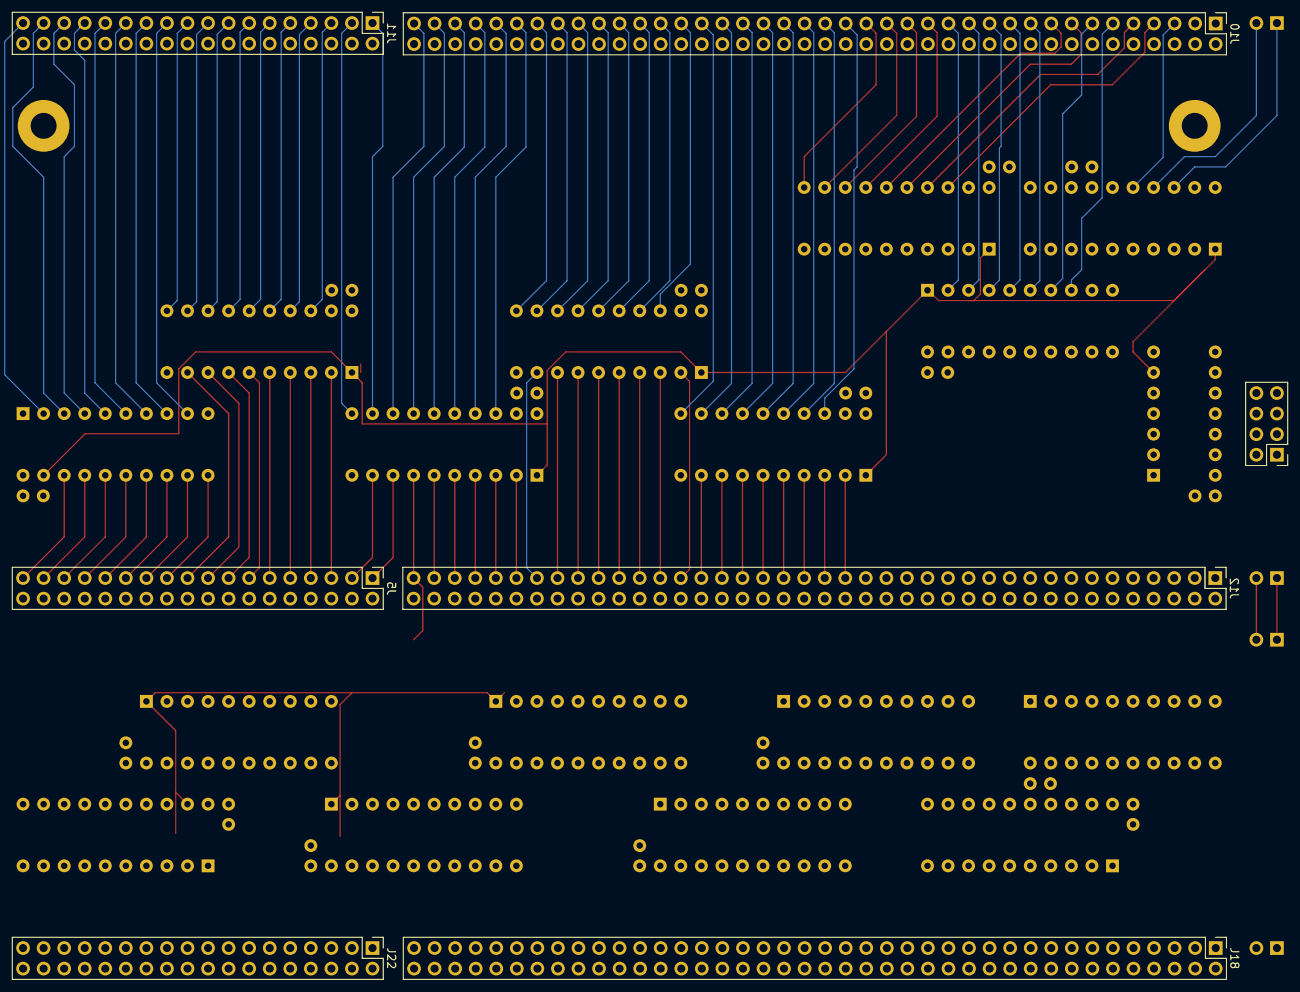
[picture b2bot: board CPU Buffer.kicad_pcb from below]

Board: 4 copper layers, 47 parts (7 on the bottom side), 184 nets.

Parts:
C1, C2, C3, C4, C5, C6, C7, C8, C9, C10, C11, C12, C13, C14, C15, C16, C17: 100n; C_Disc_D3.4mm_W2.1mm_P2.50mm
H1, H2: MountingHole_Pad; MountingHole_3.2mm_M3_Pad
J3, J6, J9, J17: VPA/VDA; PinHeader_1x02_P2.54mm_Vertical
J5: CPU AUX; PinHeader_2x18_P2.54mm_Vertical
J10, J12, J18: Conn_02x40_Odd_Even; PinHeader_2x40_P2.54mm_Vertical
J11: DMA; PinHeader_2x18_P2.54mm_Vertical
J22: DMA AUX; PinHeader_2x18_P2.54mm_Vertical
J23: Conn_02x04_Odd_Even; PinHeader_2x04_P2.54mm_Vertical
U1: 74HC00; DIP-14_W7.62mm_Socket
U2, U4, U5, U6, U7, U8, U9, U10, U11, U13, U14, U15, U16, U17: 74HC541; DIP-20_W7.62mm_Socket
U3, U12: 74AHCT245; DIP-20_W7.62mm_Socket

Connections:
/A0: J5.19, U4.9 (A7), U13.2 (A0)
/A1: J5.17, U4.8 (A6), U13.3 (A1)
/A2: J5.15, U4.7 (A5), U13.4 (A2)
/A3: J5.13, U4.6 (A4), U13.5 (A3)
/A4: J5.11, U4.5 (A3), U13.6 (A4)
/A5: J5.9, U4.4 (A2), U13.7 (A5)
/A6: J5.7, U4.3 (A1), U13.8 (A6)
/A7: J5.5, U4.2 (A0), U13.9 (A7)
/A8: J5.3, U6.9 (A7), U15.2 (A0)
/A9: J5.1, U6.8 (A6), U15.3 (A1)
/A10: J12.79, U6.7 (A5), U15.4 (A2)
/A11: J12.77, U6.6 (A4), U15.5 (A3)
/A12: J12.75, U6.5 (A3), U15.6 (A4)
/A13: J12.73, U6.4 (A2), U15.7 (A5)
/A14: J12.71, U6.3 (A1), U15.8 (A6)
/A15: J12.69, U6.2 (A0), U15.9 (A7)
/A16: J12.67, U8.9 (A7), U17.2 (A0)
/A17: J12.65, U8.8 (A6), U17.3 (A1)
/A18: J12.63, U8.7 (A5), U17.4 (A2)
/A19: J12.61, U8.6 (A4), U17.5 (A3)
/A20: J12.59, U8.5 (A3), U17.6 (A4)
/A21: J12.57, U8.4 (A2), U17.7 (A5)
/A22: J12.55, U8.3 (A1), U17.8 (A6)
/A23: J12.53, U8.2 (A0), U17.9 (A7)
/AA0: J11.19, U4.11 (Y7)
/AA1: J11.17, U4.12 (Y6)
/AA2: J11.15, U4.13 (Y5)
/AA3: J11.13, U4.14 (Y4)
/AA4: J11.11, U4.15 (Y3)
/AA5: J11.9, U4.16 (Y2)
/AA6: J11.7, U4.17 (Y1)
/AA7: J11.5, U4.18 (Y0)
/AA8: J11.3, U6.11 (Y7)
/AA9: J11.1, U6.12 (Y6)
/AA10: J10.79, U6.13 (Y5)
/AA11: J10.77, U6.14 (Y4)
/AA12: J10.75, U6.15 (Y3)
/AA13: J10.73, U6.16 (Y2)
/AA14: J10.71, U6.17 (Y1)
/AA15: J10.69, U6.18 (Y0)
/AA16: J10.67, U8.11 (Y7)
/AA17: J10.65, U8.12 (Y6)
/AA18: J10.63, U8.13 (Y5)
/AA19: J10.61, U8.14 (Y4)
/AA20: J10.59, U8.15 (Y3)
/AA21: J10.57, U8.16 (Y2)
/AA22: J10.55, U8.17 (Y1)
/AA23: J10.53, U8.18 (Y0)
/ABE: J10.25, U9.3 (A1)
/ACLK: J10.15, U5.16 (Y2)
/ACLK_SRC: J10.13, U9.7 (A5)
/AD0: J11.35, U3.2 (A0)
/AD1: J11.33, U3.3 (A1)
/AD2: J11.31, U3.4 (A2)
/AD3: J11.29, U3.5 (A3)
/AD4: J11.27, U3.6 (A4)
/AD5: J11.25, U3.7 (A5)
/AD6: J11.23, U3.8 (A6)
/AD7: J11.21, U3.9 (A7)
/AE: J10.43, U2.15 (Y3)
/AM: J10.45, U2.14 (Y4)
/ARDY_IN: J10.27, U9.2 (A0)
/ARST: J10.9, U5.17 (Y1)
/AR~W: J10.35, U5.11 (Y7)
/ASYNC: J10.31, U5.13 (Y5)
/AVA: J10.33, U5.12 (Y6)
/AVDA: J9.2, U7.17 (Y1)
/AVPA: J9.1, U7.18 (Y0)
/AX: J10.47, U2.13 (Y5)
/A_CS1: J23.1, U1.5
/BA0: J22.19, U13.18 (Y0)
/BA1: J22.17, U13.17 (Y1)
/BA2: J22.15, U13.16 (Y2)
/BA3: J22.13, U13.15 (Y3)
/BA4: J22.11, U13.14 (Y4)
/BA5: J22.9, U13.13 (Y5)
/BA6: J22.7, U13.12 (Y6)
/BA7: J22.5, U13.11 (Y7)
/BA8: J22.3, U15.18 (Y0)
/BA9: J22.1, U15.17 (Y1)
/BA10: J18.79, U15.16 (Y2)
/BA11: J18.77, U15.15 (Y3)
/BA12: J18.75, U15.14 (Y4)
/BA13: J18.73, U15.13 (Y5)
/BA14: J18.71, U15.12 (Y6)
/BA15: J18.69, U15.11 (Y7)
/BA16: J18.67, U17.18 (Y0)
/BA17: J18.65, U17.17 (Y1)
/BA18: J18.63, U17.16 (Y2)
/BA19: J18.61, U17.15 (Y3)
/BA20: J18.59, U17.14 (Y4)
/BA21: J18.57, U17.13 (Y5)
/BA22: J18.55, U17.12 (Y6)
/BA23: J18.53, U17.11 (Y7)
/BBE: J18.25, U16.7 (A5)
/BCLK: J18.15, U11.13 (Y5)
/BCLK_SRC: J18.13, U16.3 (A1)
/BD0: J22.35, U12.9 (A7)
/BD1: J22.33, U12.8 (A6)
/BD2: J22.31, U12.7 (A5)
/BD3: J22.29, U12.6 (A4)
/BD4: J22.27, U12.5 (A3)
/BD5: J22.25, U12.4 (A2)
/BD6: J22.23, U12.3 (A1)
/BD7: J22.21, U12.2 (A0)
/BE: J12.25, U9.17 (Y1), U16.13 (Y5)
/BEM: J18.43, U10.14 (Y4)
/BM: J18.45, U10.15 (Y3)
/BRDY_IN: J18.27, U16.8 (A6)
/BRST: J18.9, U11.12 (Y6)
/BR~W: J18.35, U11.18 (Y0)
/BSYNC: J18.31, U11.16 (Y2)
/BVA: J18.33, U11.17 (Y1)
/BVDA: J17.2, U14.12 (Y6)
/BVPA: J17.1, U14.11 (Y7)
/BX: J18.47, U10.16 (Y2)
/B_CS1: J23.5, U1.13
/CLK: J12.15, U5.4 (A2), U11.7 (A5)
/CLK_SRC: J12.13, U9.13 (Y5), U16.17 (Y1)
/D0: J5.35, U3.18 (B0), U12.11 (B7)
/D1: J5.33, U3.17 (B1), U12.12 (B6)
/D2: J5.31, U3.16 (B2), U12.13 (B5)
/D3: J5.29, U3.15 (B3), U12.14 (B4)
/D4: J5.27, U3.14 (B4), U12.15 (B3)
/D5: J5.25, U3.13 (B5), U12.16 (B2)
/D6: J5.23, U3.12 (B6), U12.17 (B1)
/D7: J5.21, U3.11 (B7), U12.18 (B0)
/E: J12.43, U2.5 (A3), U10.6 (A4)
/M: J12.45, U2.6 (A4), U10.5 (A3)
/RDY_IN: J12.27, U9.18 (Y0), U16.12 (Y6)
/RST: J12.9, U5.3 (A1), U11.8 (A6)
/R~W: J12.35, U3.1 (A->B), U5.9 (A7), U11.2 (A0), U12.1 (A->B)
/SYNC: J12.31, U5.7 (A5), U11.4 (A2)
/VA: J12.33, U5.8 (A6), U11.3 (A1)
/VDA: J3.2, J6.2, U7.3 (A1), U14.8 (A6)
/VPA: J3.1, J6.1, U7.2 (A0), U14.9 (A7)
/X: J12.47, U2.7 (A5), U10.4 (A2)
/~AABORT: J10.23, U9.4 (A2)
/~ABANK0: J10.41, U2.16 (Y2)
/~ABORT: J12.23, U9.16 (Y2), U16.14 (Y4)
/~ACLK_EN: J10.11, U9.8 (A6)
/~ACLK: J10.17, U5.15 (Y3)
/~AIRQ: J10.19, U9.6 (A4)
/~AML: J10.51, U2.11 (Y7)
/~AMR⎒: J10.5, U7.16 (Y2)
/~ANMI: J10.21, U9.5 (A3)
/~ARD: J10.37, U2.18 (Y0)
/~ARST: J10.7, U5.18 (Y0)
/~AVP: J10.49, U2.12 (Y6)
/~AWAI: J10.29, U5.14 (Y4)
/~AWR: J10.39, U2.17 (Y1)
/~A_CS2: J23.3, U1.1, U1.2
/~A_DMA: U1.6, U2.1 (G1), U3.19 (CE), U4.1 (G1), U5.1 (G1), U6.1 (G1), U7.1 (G1), U8.1 (G1), U9.1 (G1)
/~BABORT: J18.23, U16.6 (A4)
/~BANK0: J12.41, U2.4 (A2), U10.7 (A5)
/~BBANK0: J18.41, U10.13 (Y5)
/~BCLK_EN: J18.11, U16.2 (A0)
/~BCLK: J18.17, U11.14 (Y4)
/~BIRQ: J18.19, U16.4 (A2)
/~BML: J18.51, U10.18 (Y0)
/~BMR⎒: J18.5, U14.13 (Y5)
/~BNMI: J18.21, U16.5 (A3)
/~BRD: J18.37, U10.11 (Y7)
/~BRST: J18.7, U11.11 (Y7)
/~BVP: J18.49, U10.17 (Y1)
/~BWAI: J18.29, U11.15 (Y3)
/~BWR: J18.39, U10.12 (Y6)
/~B_CS2: J23.7, U1.9, U1.10
/~B_DMA: U1.11, U10.1 (G1), U11.1 (G1), U12.19 (CE), U13.1 (G1), U14.1 (G1), U15.1 (G1), U16.1 (G1), U17.1 (G1)
/~CLK_EN: J12.11, U9.12 (Y6), U16.18 (Y0)
/~CLK: J12.17, U5.5 (A3), U11.6 (A4)
/~IRQ: J12.19, U9.14 (Y4), U16.16 (Y2)
/~ML: J12.51, U2.9 (A7), U10.2 (A0)
/~MR⎒: J12.5, U7.4 (A2), U14.7 (A5)
/~NMI: J12.21, U9.15 (Y3), U16.15 (Y3)
/~RD: J12.37, U2.2 (A0), U10.9 (A7)
/~RST: J12.7, U5.2 (A0), U11.9 (A7)
/~VP: J12.49, U2.8 (A6), U10.3 (A1)
/~WAI: J12.29, U5.6 (A4), U11.5 (A3)
/~WR: J12.39, U2.3 (A1), U10.8 (A6)
GND: C1.2, C2.2, C3.2, C4.2, C5.2, C6.2, C7.2, C8.2, C9.2, C10.2, C11.2, C12.2, C13.2, C14.2, C15.2, C16.2, C17.2, H1.1, H2.1, J5.2, J5.4, J5.6, J5.8, J5.10, J5.12, J5.14, J5.16, J5.18, J5.20, J5.22, J5.24, J5.26, J5.28, J5.30, J5.32, J5.34, J5.36, J10.2, J10.3, J10.4, J10.6, J10.8, J10.10, J10.12, J10.14, J10.16, J10.18, J10.20, J10.22, J10.24, J10.26, J10.28, J10.30, J10.32, J10.34, J10.36, J10.38, J10.40, J10.42, J10.44, J10.46, J10.48, J10.50, J10.52, J10.54, J10.56, J10.58, J10.60, J10.62, J10.64, J10.66, J10.68, J10.70, J10.72, J10.74, J10.76, J10.78, J10.80, J11.2, J11.4, J11.6, J11.8, J11.10, J11.12, J11.14, J11.16, J11.18, J11.20, J11.22, J11.24, J11.26, J11.28, J11.30, J11.32, J11.34, J11.36, J12.2, J12.3, J12.4, J12.6, J12.8, J12.10, J12.12, J12.14, J12.16, J12.18, J12.20, J12.22, J12.24, J12.26, J12.28, J12.30, J12.32, J12.34, J12.36, J12.38, J12.40, J12.42, J12.44, J12.46, J12.48, J12.50, J12.52, J12.54, J12.56, J12.58, J12.60, J12.62, J12.64, J12.66, J12.68, J12.70, J12.72, J12.74, J12.76, J12.78, J12.80, J18.2, J18.3, J18.4, J18.6, J18.8, J18.10, J18.12, J18.14, J18.16, J18.18, J18.20, J18.22, J18.24, J18.26, J18.28, J18.30, J18.32, J18.34, J18.36, J18.38, J18.40, J18.42, J18.44, J18.46, J18.48, J18.50, J18.52, J18.54, J18.56, J18.58, J18.60, J18.62, J18.64, J18.66, J18.68, J18.70, J18.72, J18.74, J18.76, J18.78, J18.80, J22.2, J22.4, J22.6, J22.8, J22.10, J22.12, J22.14, J22.16, J22.18, J22.20, J22.22, J22.24, J22.26, J22.28, J22.30, J22.32, J22.34, J22.36, J23.2, J23.4, J23.6, J23.8, U1.7 (GND), U2.10 (GND), U2.19 (G2), U3.10 (GND), U4.10 (GND), U4.19 (G2), U5.10 (GND), U5.19 (G2), U6.10 (GND), U6.19 (G2), U7.5 (A3), U7.6 (A4), U7.7 (A5), U7.8 (A6), U7.9 (A7), U7.10 (GND), U7.19 (G2), U8.10 (GND), U8.19 (G2), U9.9 (A7), U9.10 (GND), U9.19 (G2), U10.10 (GND), U10.19 (G2), U11.10 (GND), U11.19 (G2), U12.10 (GND), U13.10 (GND), U13.19 (G2), U14.2 (A0), U14.3 (A1), U14.4 (A2), U14.5 (A3), U14.6 (A4), U14.10 (GND), U14.19 (G2), U15.10 (GND), U15.19 (G2), U16.9 (A7), U16.10 (GND), U16.19 (G2), U17.10 (GND), U17.19 (G2)
unnamed: U1.3, U1.4
unnamed: U1.8, U1.12
VCC: C1.1, C2.1, C3.1, C4.1, C5.1, C6.1, C7.1, C8.1, C9.1, C10.1, C11.1, C12.1, C13.1, C14.1, C15.1, C16.1, C17.1, J10.1, J12.1, J18.1, U1.14 (VCC), U2.20 (VCC), U3.20 (VCC), U4.20 (VCC), U5.20 (VCC), U6.20 (VCC), U7.20 (VCC), U8.20 (VCC), U9.20 (VCC), U10.20 (VCC), U11.20 (VCC), U12.20 (VCC), U13.20 (VCC), U14.20 (VCC), U15.20 (VCC), U16.20 (VCC), U17.20 (VCC)

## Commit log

2023-06-01 Upload Kicad
2023-06-01 Schematics
2023-06-01 images
2023-06-05 Update CPU Buffer
2023-06-05 readme
2023-06-05 irq demultiplexer
2023-06-05 memory bus
2023-06-05 expansion bus breakout
2023-06-05 system controller
2023-06-05 startup config
2023-06-05 kohlbecker links.
2023-06-06 plot
2023-06-06 via port rework
2023-06-06 read
2023-06-06 devices
2023-06-10 irq shim
2023-06-10 sxvg
2023-06-10 cleanup
2023-06-10 backup
2023-06-10 sdfs
2023-06-10 xvsvd
2023-06-11 expansion port hi ram
2023-06-12 new plots
2023-06-18 xcvx
2023-06-18 git ignor
2023-07-01 Big push, Sysctl, DMA Reg
2023-07-03 push
2023-07-03 dfsg
2023-07-24 Big ol update
2023-07-24 Strip
2023-07-24 wrtolei
